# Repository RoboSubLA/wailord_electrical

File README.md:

# RoboSubLA Seaking Electrical

## Team Leads
Katherine Bonomo & Andrew Ye

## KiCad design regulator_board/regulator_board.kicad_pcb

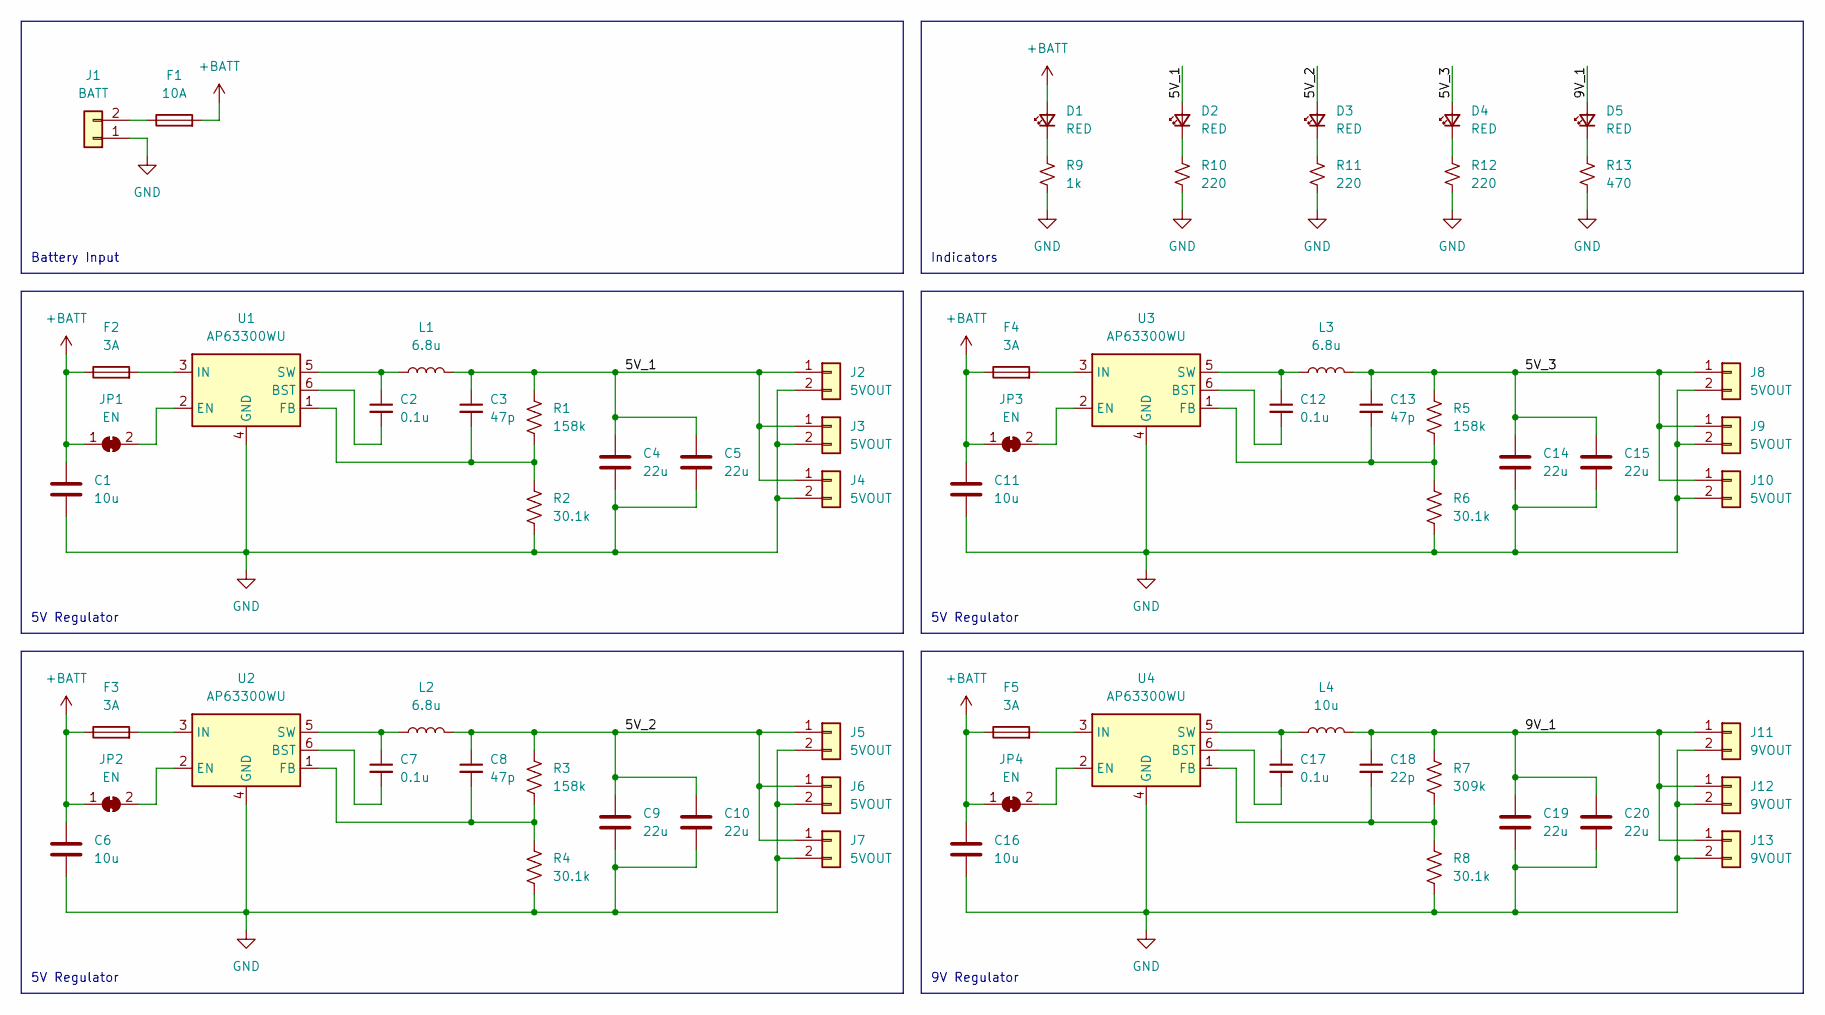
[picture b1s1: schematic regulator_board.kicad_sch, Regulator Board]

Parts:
C1, C6, C11, C16: 10u; C_0603_1608Metric_Pad1.08x0.95mm_HandSolder
C2, C7, C12, C17: 0.1u; C_0603_1608Metric_Pad1.08x0.95mm_HandSolder
C3, C8, C13: 47p; C_0603_1608Metric_Pad1.08x0.95mm_HandSolder
C4, C5, C9, C10, C14, C15, C19, C20: 22u; C_0603_1608Metric_Pad1.08x0.95mm_HandSolder
C18: 22p; C_0603_1608Metric_Pad1.08x0.95mm_HandSolder
D1, D2, D3, D4, D5: RED; LED_0603_1608Metric_Pad1.05x0.95mm_HandSolder
F1: 10A; Fuseholder_Blade_Mini_Keystone_3568
F2, F3, F4, F5: 3A; Fuse_0603_1608Metric_Pad1.05x0.95mm_HandSolder
J1: BATT; AMASS_XT60-M_1x02_P7.20mm_Vertical
J2, J3, J4, J5, J6, J7, J8, J9, J10: 5VOUT; JST_XH_B2B-XH-A_1x02_P2.50mm_Vertical
J11, J12, J13: 9VOUT; JST_XH_B2B-XH-A_1x02_P2.50mm_Vertical
JP1, JP2, JP3, JP4: EN; SolderJumper-2_P1.3mm_Bridged_RoundedPad1.0x1.5mm
L1, L2, L3: 6.8u; L_Bourns_SRP6030
L4: 10u; L_Bourns_SRP6030
R1, R3, R5: 158k; R_0603_1608Metric_Pad0.98x0.95mm_HandSolder
R2, R4, R6, R8: 30.1k; R_0603_1608Metric_Pad0.98x0.95mm_HandSolder
R7: 309k; R_0603_1608Metric_Pad0.98x0.95mm_HandSolder
R9: 1k; R_0603_1608Metric_Pad0.98x0.95mm_HandSolder
R10, R11, R12: 220; R_0603_1608Metric_Pad0.98x0.95mm_HandSolder
R13: 470; R_0603_1608Metric_Pad0.98x0.95mm_HandSolder
U1, U2, U3, U4: AP63300WU; TSOT-23-6

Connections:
+BATT: C1.1, C6.1, C11.1, C16.1, D1.2 (A), F1.2, F2.1, F3.1, F4.1, F5.1, JP1.1 (A), JP2.1 (A), JP3.1 (A), JP4.1 (A)
/5V_1: C3.1, C4.1, C5.1, D2.2 (A), J2.1, J3.1, J4.1, L1.2, R1.1
/5V_2: C8.1, C9.1, C10.1, D3.2 (A), J5.1, J6.1, J7.1, L2.2, R3.1
/5V_3: C13.1, C14.1, C15.1, D4.2 (A), J8.1, J9.1, J10.1, L3.2, R5.1
/9V_1: C18.1, C19.1, C20.1, D5.2 (A), J11.1, J12.1, J13.1, L4.2, R7.1
GND: C1.2, C4.2, C5.2, C6.2, C9.2, C10.2, C11.2, C14.2, C15.2, C16.2, C19.2, C20.2, J1.1, J2.2, J3.2, J4.2, J5.2, J6.2, J7.2, J8.2, J9.2, J10.2, J11.2, J12.2, J13.2, R2.2, R4.2, R6.2, R8.2, R9.2, R10.2, R11.2, R12.2, R13.2, U1.4 (GND), U2.4 (GND), U3.4 (GND), U4.4 (GND); also elsewhere on the board
unnamed: C2.1, L1.1, U1.5 (SW)
unnamed: C2.2, U1.6 (BST)
unnamed: C3.2, R1.2, R2.1, U1.1 (FB)
unnamed: C7.1, L2.1, U2.5 (SW)
unnamed: C7.2, U2.6 (BST)
unnamed: C8.2, R3.2, R4.1, U2.1 (FB)
unnamed: C12.1, L3.1, U3.5 (SW)
unnamed: C12.2, U3.6 (BST)
unnamed: C13.2, R5.2, R6.1, U3.1 (FB)
unnamed: C17.1, L4.1, U4.5 (SW)
unnamed: C17.2, U4.6 (BST)
unnamed: C18.2, R7.2, R8.1, U4.1 (FB)
unnamed: D1.1 (K), R9.1
unnamed: D2.1 (K), R10.1
unnamed: D3.1 (K), R11.1
unnamed: D4.1 (K), R12.1
unnamed: D5.1 (K), R13.1
unnamed: F1.1, J1.2
unnamed: F2.2, U1.3 (IN)
unnamed: F3.2, U2.3 (IN)
unnamed: F4.2, U3.3 (IN)
unnamed: F5.2, U4.3 (IN)
unnamed: JP1.2 (B), U1.2 (EN)
unnamed: JP2.2 (B), U2.2 (EN)
unnamed: JP3.2 (B), U3.2 (EN)
unnamed: JP4.2 (B), U4.2 (EN)

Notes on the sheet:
Indicators
Battery Input
5V Regulator
9V Regulator

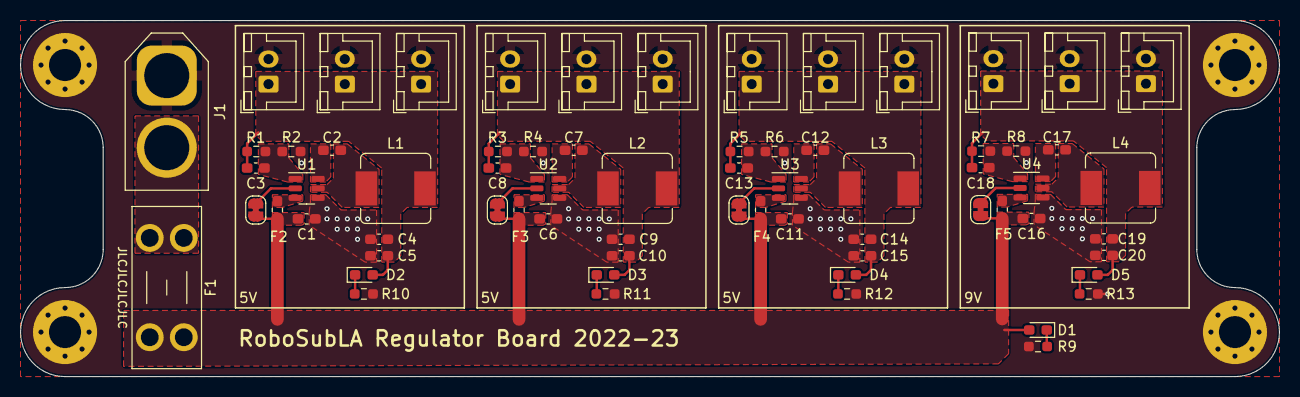
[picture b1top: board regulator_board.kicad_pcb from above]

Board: 2 copper layers, 125.7 x 35.6 mm, 73 parts (1 on the bottom side), 32 nets.

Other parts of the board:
H1, H2, H3, H4: MountingHole_Pad; MountingHole_3.2mm_M3_Pad_Via
LOGO1: Logo_Open_Hardware_Large; OSHW-Logo2_9.8x8mm_SilkScreen

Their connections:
GND: H1.1, H2.1, H3.1, H4.1; also elsewhere on the board

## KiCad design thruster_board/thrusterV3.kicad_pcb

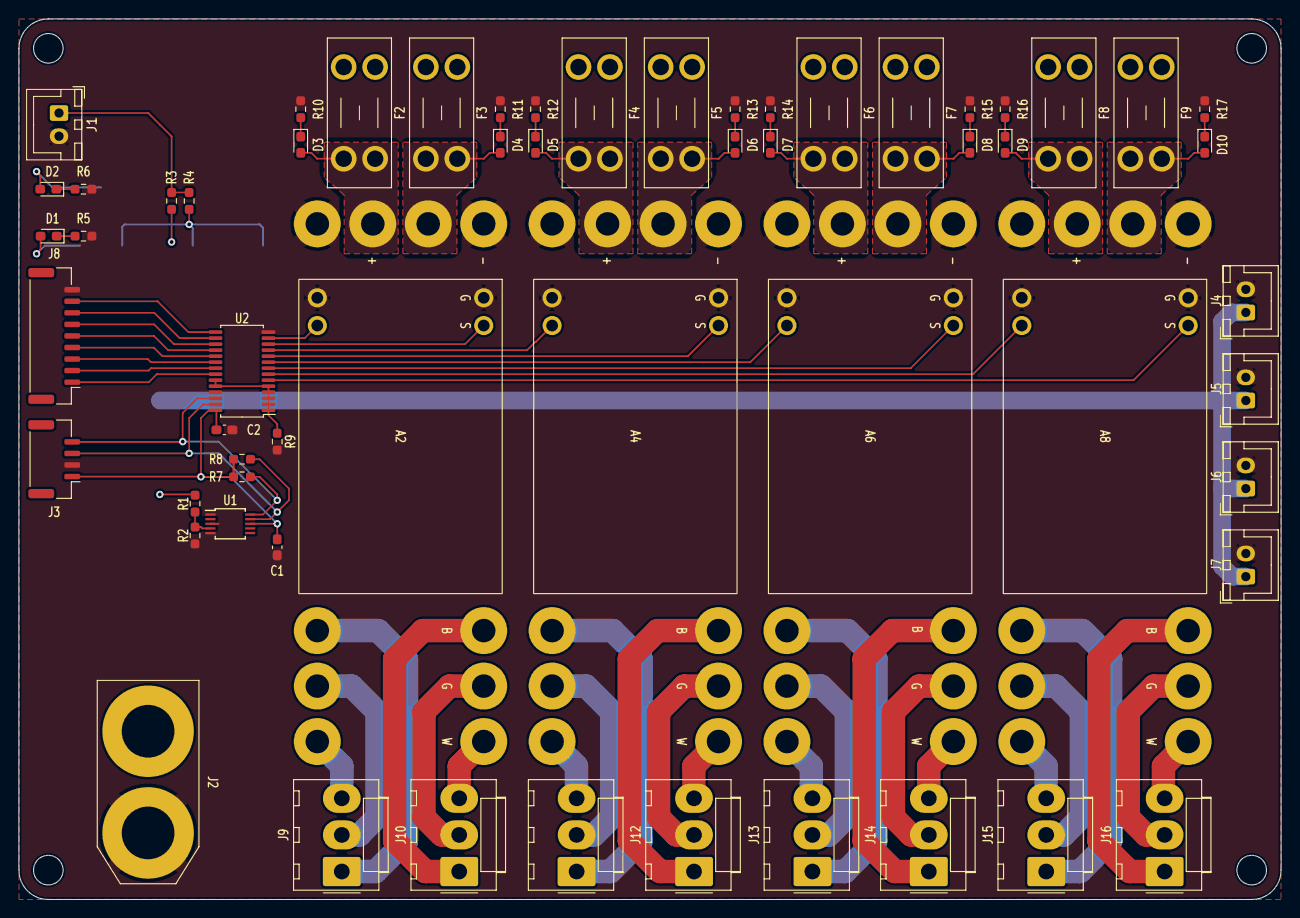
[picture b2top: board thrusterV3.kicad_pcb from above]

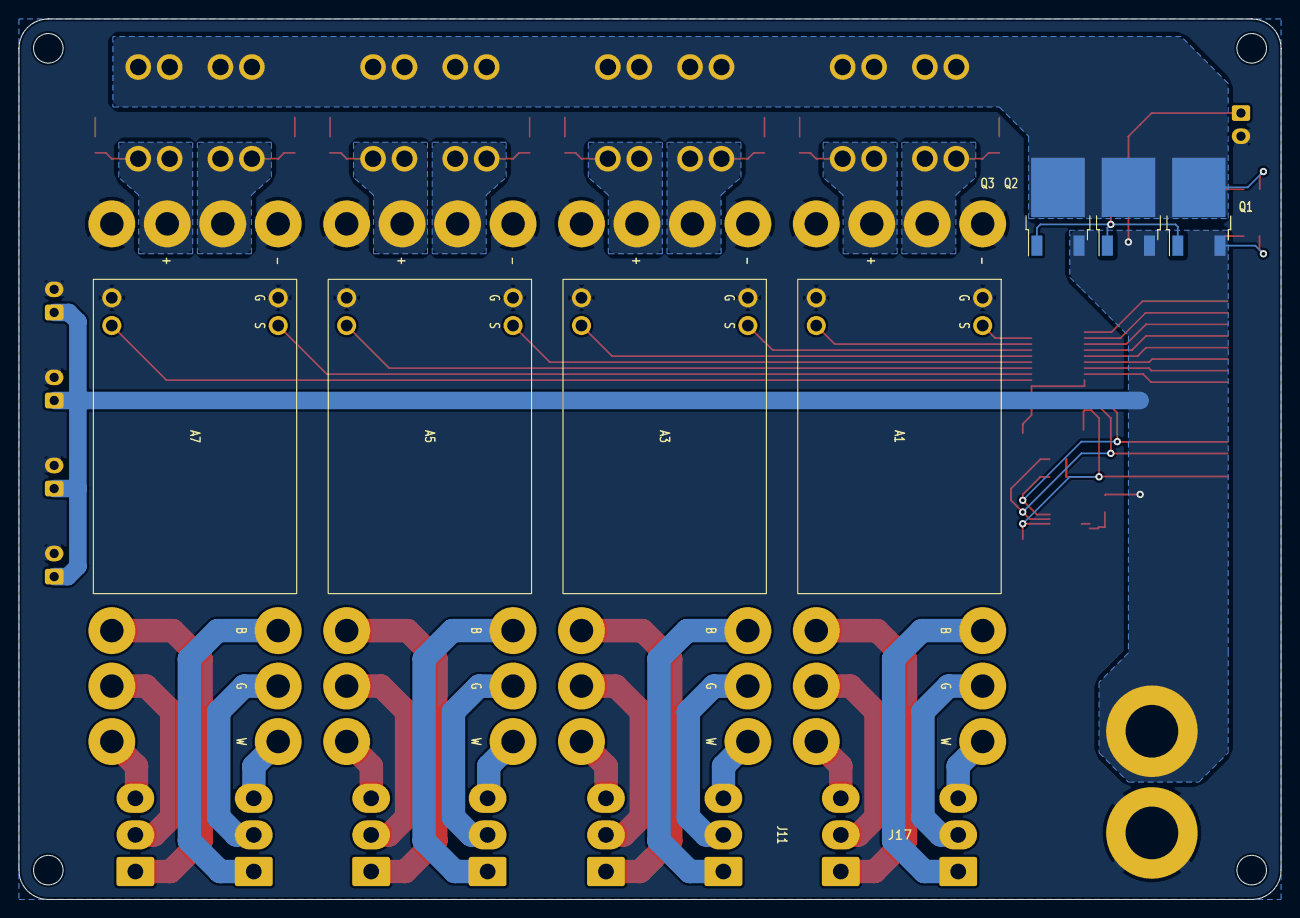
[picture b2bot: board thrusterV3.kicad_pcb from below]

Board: 4 copper layers, 136.5 x 95.3 mm, 70 parts (7 on the bottom side), 68 nets.

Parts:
A1, A2, A3, A4, A5, A6, A7, A8: BasicESC
C1, C2: 0.1u; C_0603_1608Metric_Pad1.08x0.95mm_HandSolder
D1, D3, D4, D5, D6, D7, D8, D9, D10: PWR; LED_0603_1608Metric_Pad1.05x0.95mm_HandSolder
D2: ARM; LED_0603_1608Metric_Pad1.05x0.95mm_HandSolder
F2, F3, F4, F5, F6, F7, F8, F9: 20A; Fuseholder_Blade_Mini_Keystone_3568
H1, H2, H3, H4: MountingHole; MountingHole_3.2mm_M3
J1: KS; JST_XH_B2B-XH-A_1x02_P2.50mm_Vertical
J2: BATT; XT90
J3: I2C; JST_GH_BM04B-GHS-TBT_1x04-1MP_P1.25mm_Vertical
J4: P1; JST_XH_B2B-XH-A_1x02_P2.50mm_Vertical
J5: P2; JST_XH_B2B-XH-A_1x02_P2.50mm_Vertical
J6: P3; JST_XH_B2B-XH-A_1x02_P2.50mm_Vertical
J7: P4; JST_XH_B2B-XH-A_1x02_P2.50mm_Vertical
J8: PWM; JST_GH_BM09B-GHS-TBT_1x09-1MP_P1.25mm_Vertical
J9: T1; Molex_KK-396_A-41791-0003_1x03_P3.96mm_Vertical
J10: T2; Molex_KK-396_A-41791-0003_1x03_P3.96mm_Vertical
J11: T3; Molex_KK-396_A-41791-0003_1x03_P3.96mm_Vertical
J12: T4; Molex_KK-396_A-41791-0003_1x03_P3.96mm_Vertical
J13: T5; Molex_KK-396_A-41791-0003_1x03_P3.96mm_Vertical
J14: T6; Molex_KK-396_A-41791-0003_1x03_P3.96mm_Vertical
J15: T7; Molex_KK-396_A-41791-0003_1x03_P3.96mm_Vertical
J16: T8; Molex_KK-396_A-41791-0003_1x03_P3.96mm_Vertical
Q1, Q2, Q3: SUD50P08; TO-252-2
R1, R3: 68k; R_0603_1608Metric_Pad0.98x0.95mm_HandSolder
R2: 15k; R_0603_1608Metric_Pad0.98x0.95mm_HandSolder
R4, R7, R8, R9: 4.7k; R_0603_1608Metric_Pad0.98x0.95mm_HandSolder
R5, R6, R10, R11, R12, R13, R14, R15, R16, R17: 820; R_0603_1608Metric_Pad0.98x0.95mm_HandSolder
U1: ADS1113IDGS; TSSOP-10_3x3mm_P0.5mm
U2: PCA9685PW; TSSOP-28_4.4x9.7mm_P0.65mm

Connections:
+3.3V: C1.1, C2.1, J3.1, R7.2, R8.2, U1.8 (VDD), U2.28 (VDD)
+ARM: D2.2 (A), F2.1, F3.1, F4.1, F5.1, F6.1, F7.1, F8.1, F9.1, Q1.2 (D), Q2.2 (D), Q3.2 (D)
+BATT: D1.2 (A), J2.1, J4.1, J5.1, J6.1, J7.1, Q1.3 (S), Q2.3 (S), Q3.3 (S), R1.1, R3.2
/E1: J8.8, U2.15 (LED8)
/E2: J8.7, U2.16 (LED9)
/E3: J8.6, U2.17 (LED10)
/E4: J8.5, U2.18 (LED11)
/E5: J8.4, U2.19 (LED12)
/E6: J8.3, U2.20 (LED13)
/E7: J8.2, U2.21 (LED14)
/E8: J8.1, U2.22 (LED15)
/ESC1/+: A1.2 (+), D3.2 (A), F2.2
/ESC1/B: A1.3 (B), J9.1
/ESC1/G: A1.4 (G), J9.2
/ESC1/W: A1.5 (W), J9.3
/ESC2/+: A2.2 (+), D4.2 (A), F3.2
/ESC2/B: A2.3 (B), J10.1
/ESC2/G: A2.4 (G), J10.2
/ESC2/W: A2.5 (W), J10.3
/ESC3/+: A3.2 (+), D5.2 (A), F4.2
/ESC3/B: A3.3 (B), J11.1
/ESC3/G: A3.4 (G), J11.2
/ESC3/W: A3.5 (W), J11.3
/ESC4/+: A4.2 (+), D6.2 (A), F5.2
/ESC4/B: A4.3 (B), J12.1
/ESC4/G: A4.4 (G), J12.2
/ESC4/W: A4.5 (W), J12.3
/ESC5/+: A5.2 (+), D7.2 (A), F6.2
/ESC5/B: A5.3 (B), J13.1
/ESC5/G: A5.4 (G), J13.2
/ESC5/W: A5.5 (W), J13.3
/ESC6/+: A6.2 (+), D8.2 (A), F7.2
/ESC6/B: A6.3 (B), J14.1
/ESC6/G: A6.4 (G), J14.2
/ESC6/W: A6.5 (W), J14.3
/ESC7/+: A7.2 (+), D9.2 (A), F8.2
/ESC7/B: A7.3 (B), J15.1
/ESC7/G: A7.4 (G), J15.2
/ESC7/W: A7.5 (W), J15.3
/ESC8/+: A8.2 (+), D10.2 (A), F9.2
/ESC8/B: A8.3 (B), J16.1
/ESC8/G: A8.4 (G), J16.2
/ESC8/W: A8.5 (W), J16.3
/PWM1: A1.6 (PWM+), U2.13 (LED7)
/PWM2: A2.6 (PWM+), U2.12 (LED6)
/PWM3: A3.6 (PWM+), U2.11 (LED5)
/PWM4: A4.6 (PWM+), U2.10 (LED4)
/PWM5: A5.6 (PWM+), U2.9 (LED3)
/PWM6: A6.6 (PWM+), U2.8 (LED2)
/PWM7: A7.6 (PWM+), U2.7 (LED1)
/PWM8: A8.6 (PWM+), U2.6 (LED0)
/SCL: J3.4, R7.1, U1.10 (SCL), U2.26 (SCL)
/SDA: J3.3, R8.1, U1.9 (SDA), U2.27 (SDA)
/~KS: Q1.1 (G), Q2.1 (G), Q3.1 (G), R4.1
GND: A1.1 (-), A1.7 (PWM-), A2.1 (-), A2.7 (PWM-), A3.1 (-), A3.7 (PWM-), A4.1 (-), A4.7 (PWM-), A5.1 (-), A5.7 (PWM-), A6.1 (-), A6.7 (PWM-), A7.1 (-), A7.7 (PWM-), A8.1 (-), A8.7 (PWM-), C1.2, C2.2, J1.2, J2.2, J3.2, J4.2, J5.2, J6.2, J7.2, J8.9, R2.2, R5.2, R6.2, R9.2, R10.1, R11.1, R12.1, R13.1, R14.1, R15.1, R16.1, R17.1, U1.1 (ADDR), U1.3 (GND), U1.5 (AIN1), U2.14 (VSS), U2.25 (EXTCLK)
unnamed: D1.1 (K), R5.1
unnamed: D2.1 (K), R6.1
unnamed: D3.1 (K), R10.2
unnamed: D4.1 (K), R11.2
unnamed: D5.1 (K), R12.2
unnamed: D6.1 (K), R13.2
unnamed: D7.1 (K), R14.2
unnamed: D8.1 (K), R15.2
unnamed: D9.1 (K), R16.2
unnamed: D10.1 (K), R17.2
unnamed: J1.1, R3.1, R4.2
unnamed: R1.2, R2.1, U1.4 (AIN0)
unnamed: R9.1, U2.1 (A0), U2.2 (A1), U2.3 (A2), U2.4 (A3), U2.5 (A4), U2.23 (~OE), U2.24 (A5)

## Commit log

2022-09-16 Readme & License
2022-09-16 Fix Readme Title
2022-09-24 Vehicle rename
2022-10-18 thruster board upload
2023-01-11 cleanup repo, add .gitignore, regulator board d1
2023-01-11 regulator board title block
2023-01-13 regulator component footprints
2023-01-13 gitignore update
2023-01-13 regulator design preliminary
2023-01-13 regulator board prelimiary completion
2023-01-15 fix regulator xt60 orientation
2023-01-15 regulator silkscreen and models
2023-02-02 regulator board outline redesign & back graphics
2023-02-02 one final graphic
2023-02-02 regulator board gerbers export
2023-02-02 add order number position
2023-02-02 inductor 3d models
